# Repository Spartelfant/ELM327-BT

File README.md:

There's not much here yet unfortunately :( I do hope to get around to adding some proper documentation at some point. Until that time, I have listed some important bits of information down below.

- This board is designed around the ELM327 v2.1 and also compatible with v2.2. If you're going to use a newer firmware version, please check the changelog and / or compare its documentation to the v2.1 datasheet to check for compatibility.
- The ELM327**L** is **not** pin-compatible with the ELM327, even though it has the same features in the same package. On the ELM327 (what this board is designed for) pin 6 can be pulled high or low to set the RS232 baud rate on powerup / reset. On the ELM327**L** there should be a capacitor (10uF tantalum or ceramic with low ESR, less than 5 Ohms) between pin 6 and GND. If you do pick the ELM327**L** I recommend you either replace the header with a capacitor footprint in the schematic and pcb layout or simply stick a capacitor in the header footprint during production.
- I have built this design myself and it works properly, although so far I have only been able to test it with the ISO14230 protocol which uses the K-line and optionally the L-line for communication with the car.
- The LP2951 (less current and shutdown capability) is a replacement for the 317L (as suggested in the ELM327 datasheet), but its logic is inverted. So after building the project you must send the following configuration commands to the ELM327 (this is a one-time thing): `AT PP 12 SV 00` and `AT PP 12 ON`. Failure to do so will not do any damage, however SAE J1850 PWM (Ford) and SAE J1850 VPW (GM) communication will not work and may interfere with the car's communication bus.
- When selecting a Bluetooth module, pay attention to its voltage levels. This pcb is designed to supply 5V to the module and has a voltage divider in the ELM327's TX line to communicate at 3V3. The reason for this seemingly odd design is that 5V power & data BT modules are few and far between, yet I wanted to avoid squeezing a 3V3 supply on the board just for the module. While a voltage divider in the ELM327's TX line is not as elegant as a proper level converter, it has worked well for me at a 38k8 baud rate (higher rates not yet tested).
- On the same note, the BT module communicating at 3V3 to the ELM327's RX line is out-of-spec for the ELM327. Its RX input pin is configured to use Schmitt trigger waveshaping and therefore requires an input voltage between 2V9 (typical) and 4V (maximum) to register a HIGH input. So it *can* work and in my experience often does, but it's not exactly the most robust design choice. That would be to use a level converter circuit.
- While on the subject of Bluetooth modules, I opted for Bluetooth version 2.0+EDR. Another widely available option is Bluetooth version 4.0BLE, but the BLE (Bluetooth Low Energy) part makes it less suited for this project. It's a protocol intended for short communications (like reading a temperature sensor once a minute), it's not designed with a continuous connection in mind. It's also not always supported by older devices. Consequently, you may have trouble connecting to a BLE module for this project, even when using a device with support for it.

If you have any questions or feedback, feel free to send me an email at [my Github username]@gmail.com.

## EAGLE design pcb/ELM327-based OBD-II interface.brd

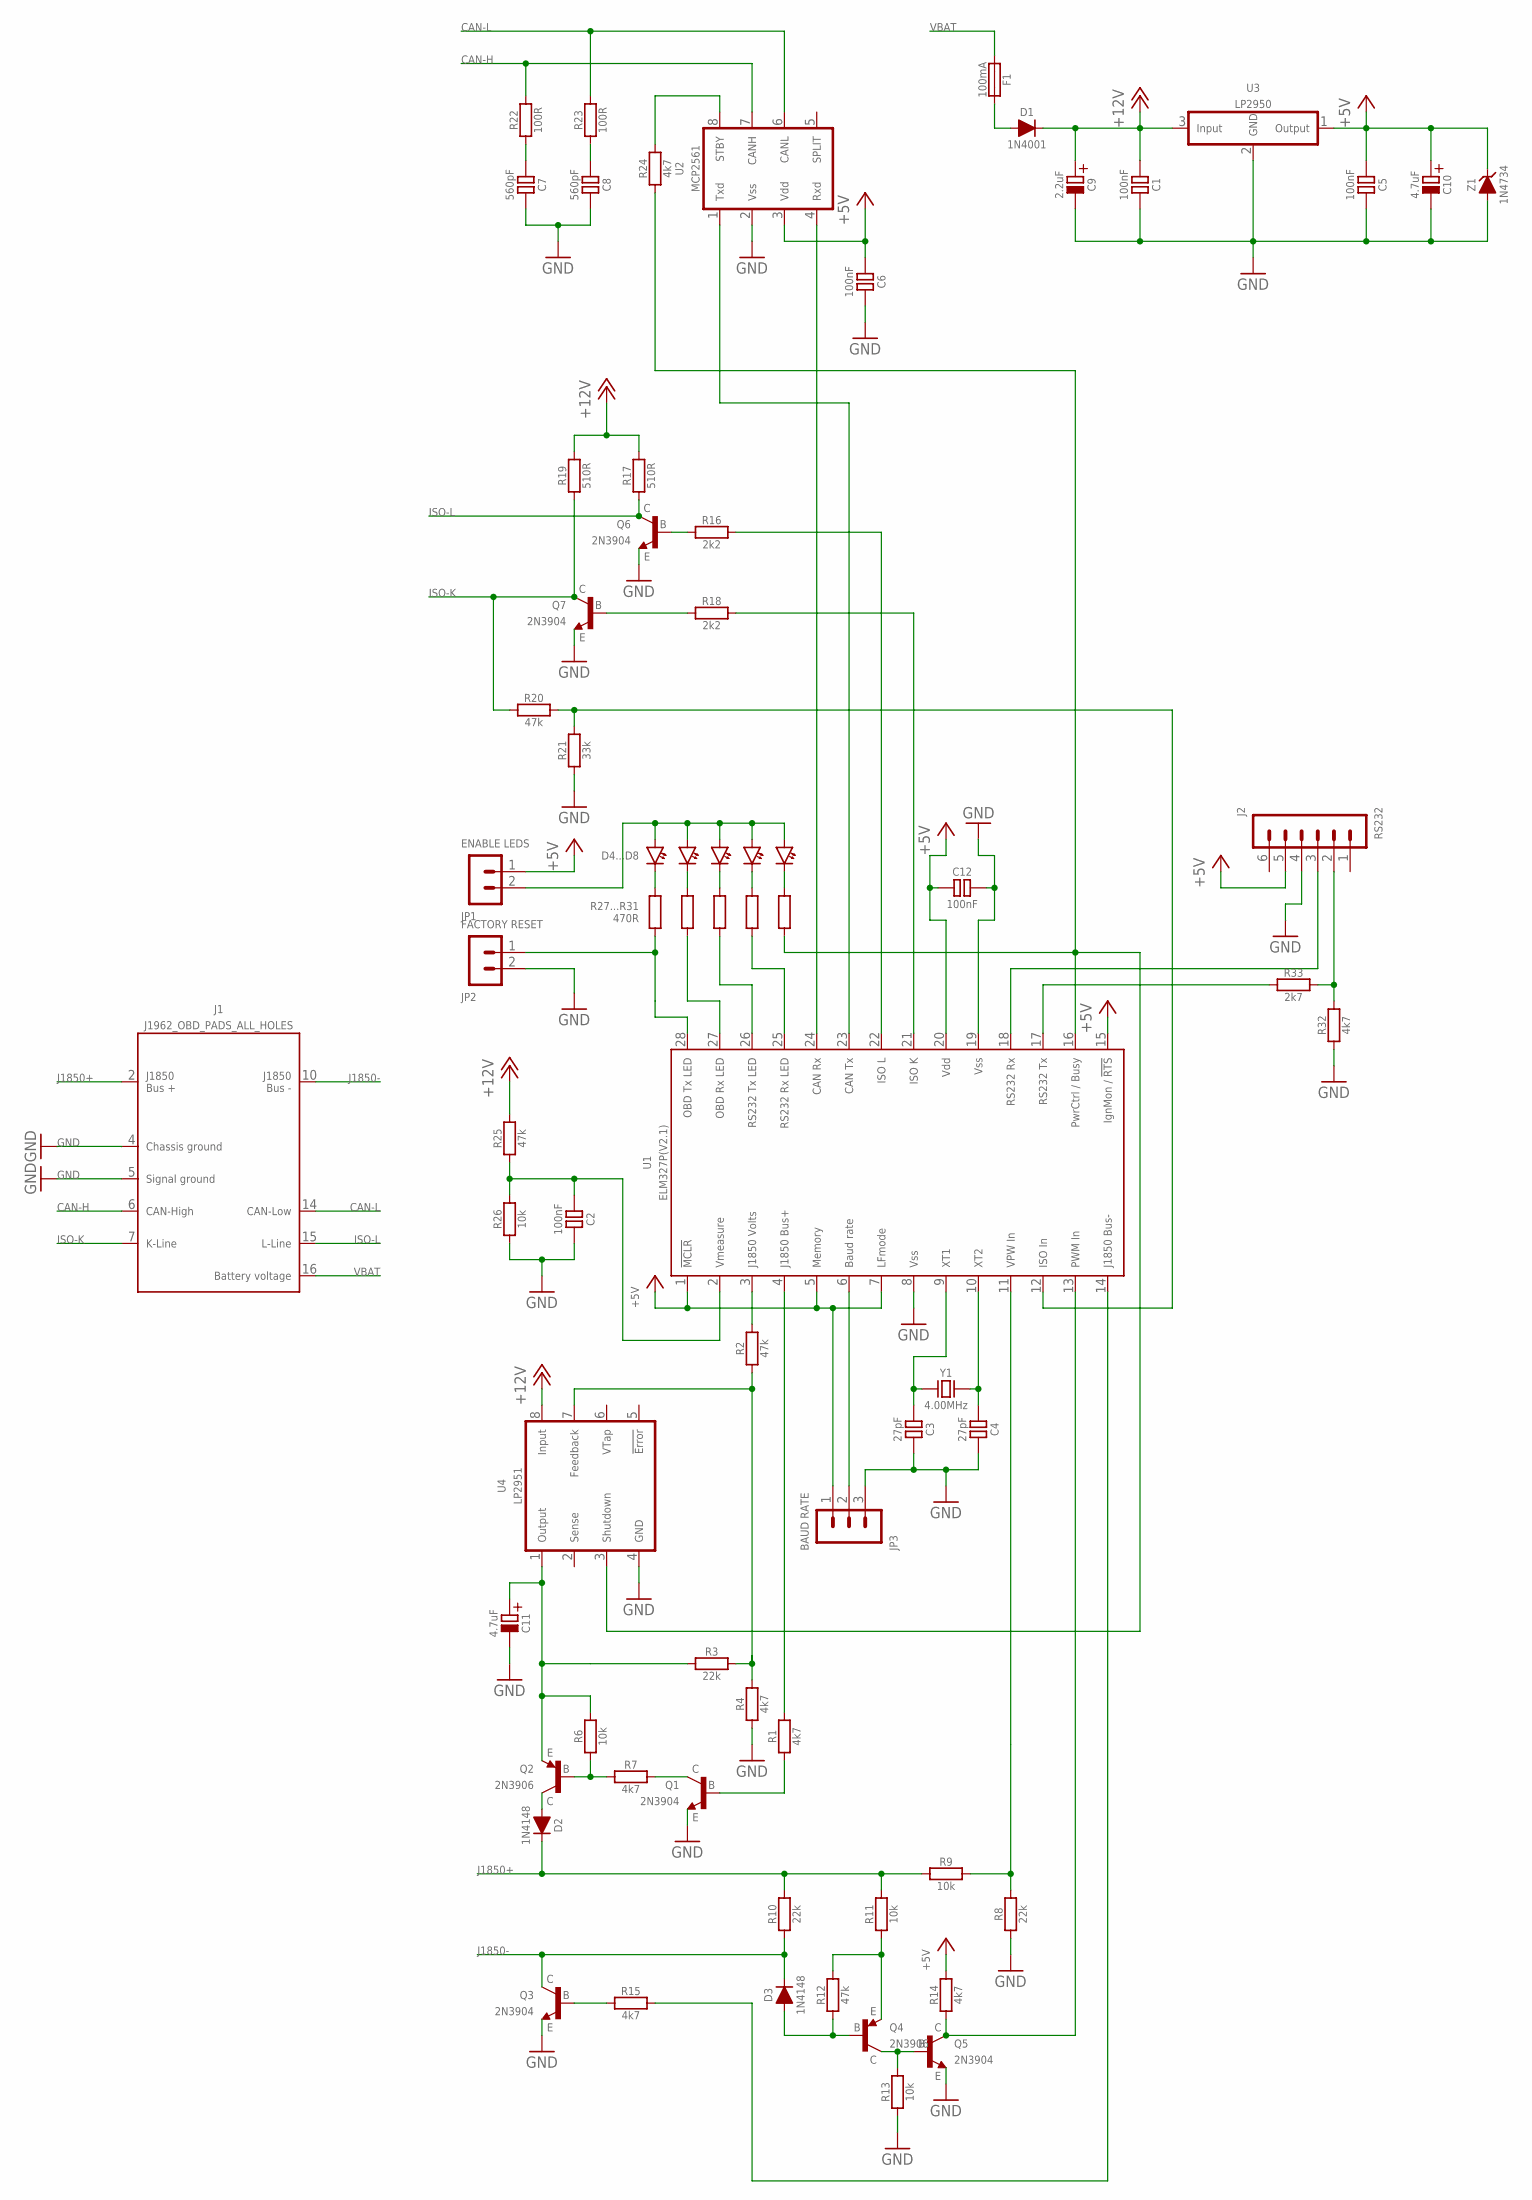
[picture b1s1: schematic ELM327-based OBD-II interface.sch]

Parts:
C1, C2, C5, C6, C12: 100nF; MLCC-5.08
C3, C4: 27pF; MLCC-5.08
C7, C8: 560pF; MLCC-5.08
C9: 2.2uF; E2-5
C10, C11: 4.7uF; TANTALUM-5.08
D1: 1N4001; DO-41
D2, D3: 1N4148; DO-35
D4: OBD Tx; LED_5MM
D5: OBD Rx; LED_5MM
D6: RS232 Tx; LED_5MM
D7: RS232 Rx; LED_5MM
D8: ON; LED_5MM
F1: 100mA; FUSE
J1: J1962_OBD_PADS_ALL_HOLES
J2: RS232; HEADER_1X6
JP1: ENABLE LEDS; HEADER_1X2
JP2: FACTORY RESET; HEADER_1X2
JP3: BAUD RATE; HEADER_1X3
Q1, Q3, Q5, Q6, Q7: 2N3904; TO-92
Q2, Q4: 2N3906; TO-92
R1, R4, R7, R14, R15, R24, R32: 4k7; MF12-1/8W
R2, R12, R20, R25: 47k; MF12-1/8W
R3, R8, R10: 22k; MF12-1/8W
R6, R9, R11, R13, R26: 10k; MF12-1/8W
R16, R18: 2k2; MF12-1/8W
R17, R19: 510R; MF50-1/2W
R21: 33k; MF12-1/8W
R22, R23: 100R; MF12-1/8W
R27, R28, R29, R30, R31: 470R; MF12-1/8W
R33: 2k7; MF12-1/8W
U1: ELM327P(V2.1); SPDIP(28)
U2: MCP2561; PDIP
U3: LP2950; TO-92
U4: LP2951; PDIP-8
Y1: 4.00MHz; HC49
Z1: 1N4734; DO-41

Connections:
+5V: C5.+, C6.+, C10.+, C12.+, J2.5, JP1.1, JP3.1, R14.2, U1.1 (!MCLR), U1.5 (MEMORY), U1.7 (LFMODE), U1.15 (IGNMON/!RTS), U1.20 (VDD), U2.3 (VDD), U3.1 (OUTPUT), Z1.C
+12V: C1.+, C9.+, D1.C, R17.2, R19.2, R25.2, U3.3 (INPUT), U4.8 (INPUT)
CAN-H: J1.6, R22.2, U2.7 (CANH)
CAN-L: J1.14, R23.2, U2.6 (CANL)
GND: C1.-, C2.-, C3.-, C4.-, C5.-, C6.-, C7.-, C8.-, C9.-, C10.-, C11.-, C12.-, J1.4, J1.5, J2.4, JP2.2, JP3.3, Q1.E, Q3.E, Q5.E, Q6.E, Q7.E, R4.1, R8.1, R13.1, R21.1, R26.1, R32.1, U1.8 (VSS), U1.19 (VSS), U2.2 (VSS), U3.2 (GND), U4.4 (GND), Z1.A
ISO-K: J1.7, Q7.C, R19.1, R20.1
ISO-L: J1.15, Q6.C, R17.1
J1850+: D2.C, J1.2, R9.1, R10.2, R11.2
J1850-: D3.C, J1.10, Q3.C, R10.1
unnamed: D4.A, D5.A, D6.A, D7.A, D8.A, JP1.2
unnamed: JP2.1, R27.1, U1.28 (OBD_TX_LED)
unnamed: R28.1, U1.27 (OBD_RX_LED)
unnamed: R29.1, U1.26 (RS232_TX_LED)
unnamed: R30.1, U1.25 (RS232_RX_LED)
unnamed: D4.C, R27.2
unnamed: D5.C, R28.2
unnamed: D6.C, R29.2
unnamed: D7.C, R30.2
unnamed: D8.C, R31.2
unnamed: U1.24 (CAN_RX), U2.4 (RXD)
unnamed: U1.23 (CAN_TX), U2.1 (TXD)
unnamed: R24.1, R31.1, U1.16 (PWRCTRL/BUSY), U4.3 (SHUTDOWN)
unnamed: C2.+, R25.1, R26.2, U1.2 (VMEASURE)
unnamed: R24.2, U2.8 (STBY)
unnamed: C7.+, R22.1
unnamed: R2.2, U1.3 (J1850_VOLTS)
unnamed: C8.+, R23.1
unnamed: Q7.B, R18.1
unnamed: Q6.B, R16.1
unnamed: R2.1, R3.2, R4.2, U4.7 (FEEDBACK)
unnamed: C11.+, Q2.E, R3.1, R6.2, U4.1 (OUTPUT)
unnamed: Q2.B, R6.1, R7.1
unnamed: D2.A, Q2.C
unnamed: Q1.C, R7.2
unnamed: Q1.B, R1.1
unnamed: R1.2, U1.4 (J1850_BUS+)
unnamed: R18.2, U1.21 (ISO_K)
unnamed: C4.+, U1.10 (XT2), Y1.2
unnamed: C3.+, U1.9 (XT1), Y1.1
unnamed: R8.2, R9.2, U1.11 (VPW_IN)
unnamed: Q3.B, R15.1
unnamed: R15.2, U1.14 (J1850_BUS-)
unnamed: D3.A, Q4.B, R12.1
unnamed: Q4.E, R11.1, R12.2
unnamed: Q4.C, Q5.B, R13.2
unnamed: Q5.C, R14.1, U1.13 (PWM_IN)
unnamed: R16.2, U1.22 (ISO_L)
unnamed: D1.A, F1.2
unnamed: R20.2, R21.2, U1.12 (ISO_IN)
unnamed: J2.3, U1.18 (RS232_RX)
unnamed: J2.2, R32.2, R33.2
unnamed: R33.1, U1.17 (RS232_TX)
unnamed: JP3.2, U1.6 (BAUD_RATE)
VBAT: F1.1, J1.16

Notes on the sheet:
D4...D8
R27...R31 470R

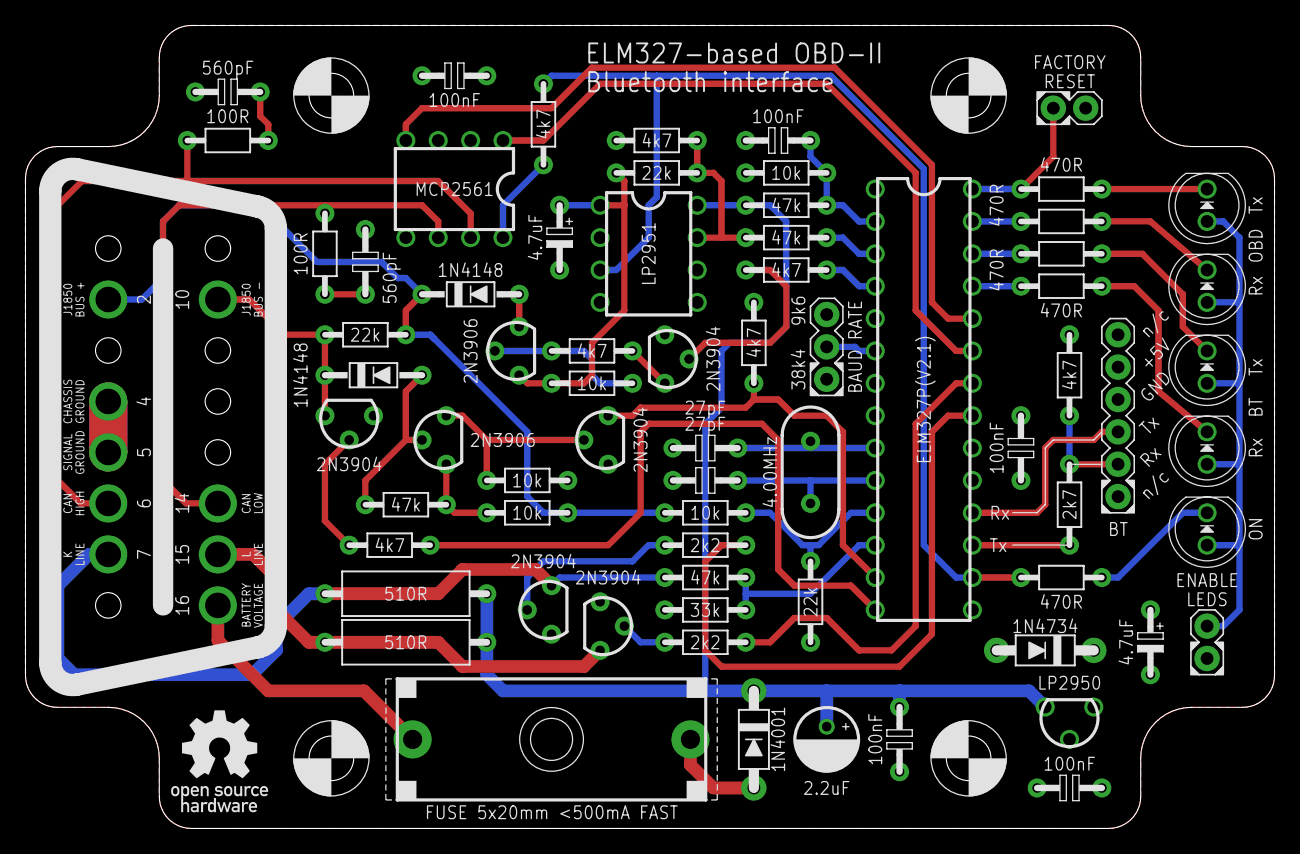
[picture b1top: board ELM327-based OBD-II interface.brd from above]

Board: 2 copper layers, 98.0 x 63.0 mm, 71 parts (0 on the bottom side), 54 nets.

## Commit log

2016-10-14 Added LICENSE.md
    Creative Commons Attribution-ShareAlike 4.0 International license
2017-01-18 Eagle files
2017-01-18 Bill of Materials
2017-01-18 Custom libraries for Eagle
2017-01-18 Relevant datasheets
2017-04-26 Added .gitignore
2017-08-09 Update README.md
    - Updated with confirmation that it actually works :)
    - Added configuration info regarding LP2951
    - Added info regarding recommended Bluetooth version
2018-01-03 Update README.md
    Added some details regarding the interfacing of a 3V3 BT module with the 5V ELM327
2020-06-01 Formatting
    Formatted the AT commands as code.

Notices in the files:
pcb/ELM327-based OBD-II interface.brd:
This work is licensed under a Creative Commons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
parts and their libraries:
Elm Electronics: This library was created 2016-09-20 by Bart Kuijper and is licensed under a Creative Commons Attribution-ShareAlike 4.0 International License.
